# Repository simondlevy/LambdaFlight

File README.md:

# LambdaFlight
LambdaFlight is a Haskell-based flight-control package for miniature aerial
vehicles (MAVs), a.k.a.drones.  It currently works with the 
[Crazyflie](https://www.bitcraze.io/products/crazyflie-2-1/)
quadcopter and
has support for Software-In-The-Loop (SITL) simulation using
[Webots](https://cyberbotics.com/).  

To try out LambdaFlight, you'll first need to install
[Haskell](https://www.haskell.org/)
and
[NASA Copilot](https://copilot-language.github.io) (the &ldquo;secret sauce&rdquo; that
allows you to compile Haskell code to a form suitable for running on a flight 
controller.)  I was able to do this via:

```
cabal install copilot
cabal install copilot-c99
```

Then you can run a simulated
quadcopter in Webots or an actual Crazyflie, following the instructions below:

## Webots

1. Install [Webots](https://cyberbotics.com/) on your computer.  

2. Launch Webots and use <b>File / Open World</b> to open <b>Minifile/webots/worlds/simple.wbt</b>.

3. In the upper-right of the Webots app you will see a label <b>Text Editor</b> with a little file-folder
icon below it.  Use that icon to open <b>Controllers/simple/simple.cpp</b>.

4.  Build and run the code.  If you have a game controller or R/C transmitter with
adapter dongle, you can use that to fly;  otherwise, the simulator will advise you
that no such device was found and will tell you how to fly using the keyboard.

## Crazyflie

LambdaFlight takes a minimalist approach, not
supporting Crayzyflie's awesome Loco positioning or swarms, and requiriing you
to have a Crazyflie Flowdeck v2, so for running your Crazyflie you'll probably
want to use the official Crazyflie firmware. If you want to try LambdaFlight
on your Crazyflie, here's how:

1. Attach the
[Crazyflie Flowdeck v2](https://www.bitcraze.io/products/flow-deck-v2/)
to your Crazyflie board.

2. Install [STM32Duino](https://github.com/stm32duino)

3. Install the following Arduino libraries:

* [VL53L1](https://github.com/simondlevy/VL53L1)
* [PWM3901](https://github.com/simondlevy/PMW3901), <b>cross-platform</b> branch
* [BoschSensors](https://github.com/simondlevy/BoschSensors)
* [TinyEKF](https://github.com/simondlevy/TinyEKF)

4. Edit <tt>LambdaFlight/crazyflie/Makefile</tt> to reflect where you 
installed STM32Duino

5. ```cd LambdaFlight/crazyflie```

6. ```make cf2_defconfig && make links && make copilot && make -j 32```

7. ```make cload```

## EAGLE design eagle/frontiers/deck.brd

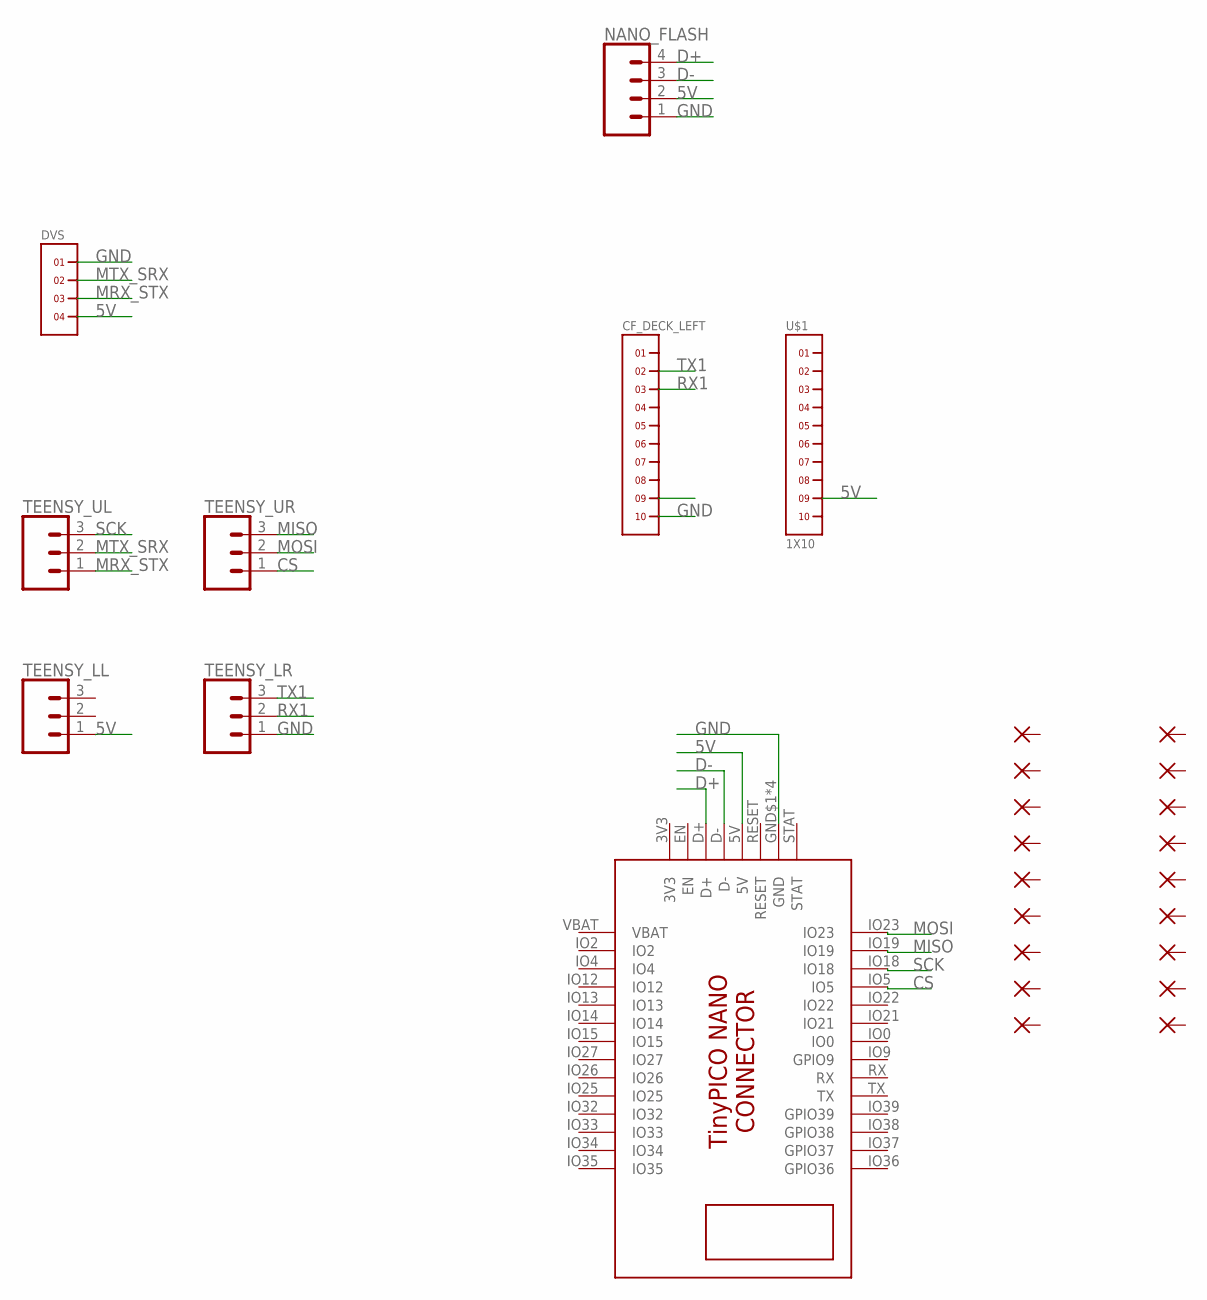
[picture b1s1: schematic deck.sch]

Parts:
CF_DECK_LEFT: 1X10
DVS: 1X4
NANO_FLASH: CONN_041X04_NO_SILK; 1X04_NO_SILK
PAD1, PAD2, PAD3, PAD4, PAD5, PAD6, PAD7, PAD8, PAD9, PAD10, PAD11, PAD12, PAD13, PAD14, PAD15, PAD16, PAD17, PAD18: SMD2; SMD1,27-2,54
TEENSY_LL: CONN_031X03_NO_SILK; 1X03_NO_SILK
TEENSY_LR: CONN_031X03_NO_SILK; 1X03_NO_SILK
TEENSY_UL: CONN_031X03_NO_SILK; 1X03_NO_SILK
TEENSY_UR: CONN_031X03_NO_SILK; 1X03_NO_SILK
U$1: 1X10
U$4: TINYPICO-NANO-CONNECTOR

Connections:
3V3: U$4.3V3
5V: DVS.4, NANO_FLASH.2, TEENSY_LL.1, U$1.9, U$4.5V
CS: TEENSY_UR.1, U$4.IO5
D+: NANO_FLASH.4, U$4.D+
D-: NANO_FLASH.3, U$4.D-
GND: CF_DECK_LEFT.10, DVS.1, NANO_FLASH.1, TEENSY_LR.1, U$4.GND$1 (GND), U$4.GND$2 (GND), U$4.GND$3 (GND), U$4.GND$4 (GND)
IO_4: CF_DECK_LEFT.9
MISO: TEENSY_UR.3, U$4.IO19
MOSI: TEENSY_UR.2, U$4.IO23
MRX_STX: DVS.3, TEENSY_UL.1
MTX_SRX: DVS.2, TEENSY_UL.2
RX1: CF_DECK_LEFT.3, TEENSY_LR.2
SCK: TEENSY_UL.3, U$4.IO18
TX1: CF_DECK_LEFT.2, TEENSY_LR.3
VBAT: U$4.VBAT

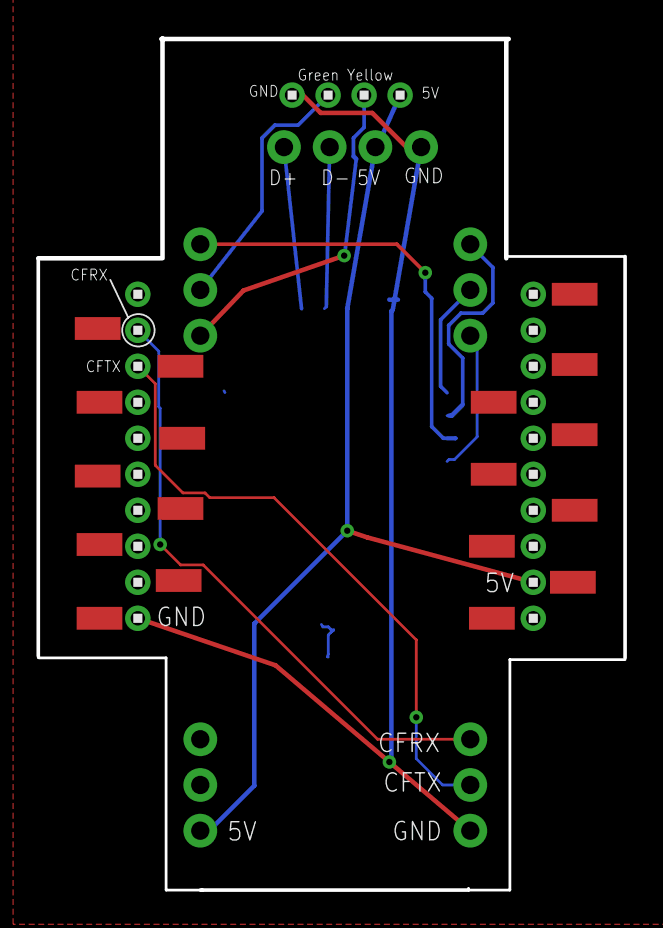
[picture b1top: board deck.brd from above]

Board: 2 copper layers, 32.6 x 47.3 mm, 27 parts (1 on the bottom side), 12 nets.

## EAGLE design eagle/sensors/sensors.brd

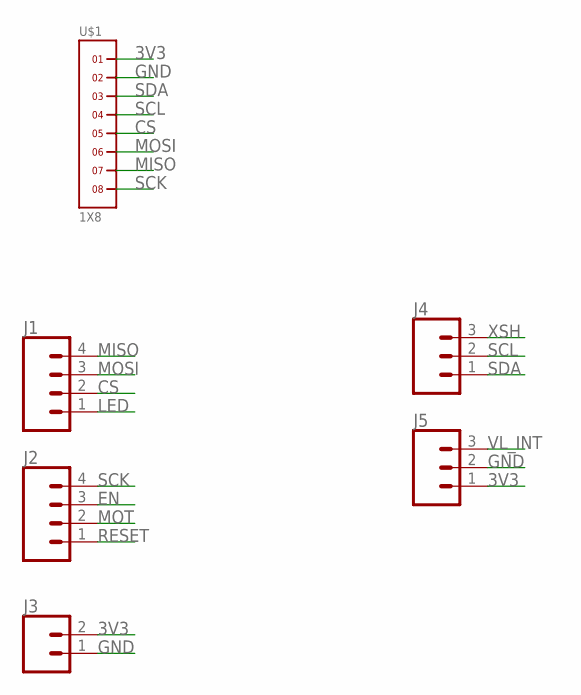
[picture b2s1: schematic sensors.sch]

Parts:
J1, J2: CONN_041X04_NO_SILK; 1X04_NO_SILK
J3: CONN_021X02_NO_SILK; 1X02_NO_SILK
J4, J5: CONN_031X03_NO_SILK; 1X03_NO_SILK
U$1: 1X8

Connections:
3V3: J3.2, J5.1, U$1.1
CS: J1.2, U$1.5
EN: J2.3
GND: J3.1, J5.2, U$1.2
LED: J1.1
MISO: J1.4, U$1.7
MOSI: J1.3, U$1.6
MOT: J2.2
RESET: J2.1
SCK: J2.4, U$1.8
SCL: J4.2, U$1.4
SDA: J4.1, U$1.3
VL_INT: J5.3
XSH: J4.3

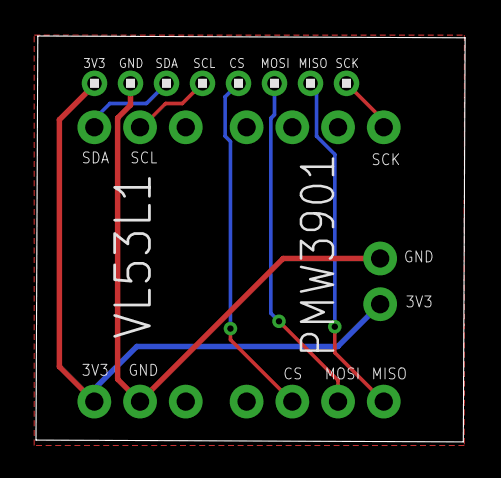
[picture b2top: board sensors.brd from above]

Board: 2 copper layers, 23.8 x 22.6 mm, 6 parts (0 on the bottom side), 8 nets.

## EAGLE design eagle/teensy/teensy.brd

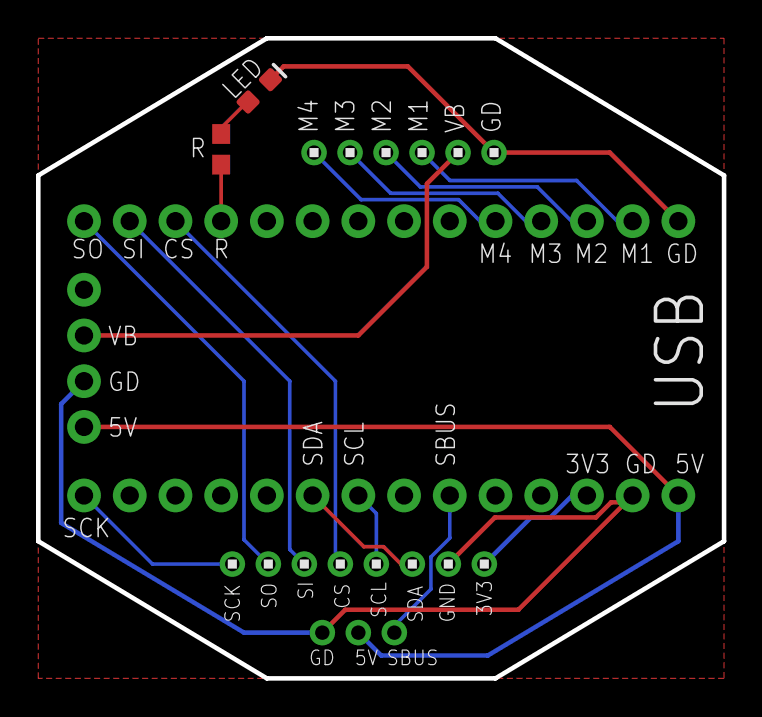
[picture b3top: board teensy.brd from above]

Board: 2 copper layers, 38.1 x 35.6 mm, 8 parts (1 on the bottom side), 17 nets.

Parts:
D1: WHITE; LED-0603
J1: 1X04_NO_SILK
J2, J3: 1X14_NO_SILK
R1: 22; 0603
U$2: 1X3
U$3: 1X8
U$4: 1X6

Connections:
3V3: J3.12, U$3.1
5V: J1.4, J3.14, U$2.2
CS: J2.3, U$3.5
GND: D1.C, J1.3, J2.14, J3.13, U$2.1, U$3.2, U$4.1
M1: J2.13, U$4.3
M2: J2.12, U$4.4
M3: J2.11, U$4.5
M4: J2.10, U$4.6
MISO: J2.1, U$3.7
MOSI: J2.2, U$3.6
R1: J2.4, R1.1
R2: D1.A, R1.2
SBUS: J3.9, U$2.3
SCK: J3.1, U$3.8
SCL: J3.7, U$3.4
SDA: J3.6, U$3.3
VBAT: J1.2, U$4.2

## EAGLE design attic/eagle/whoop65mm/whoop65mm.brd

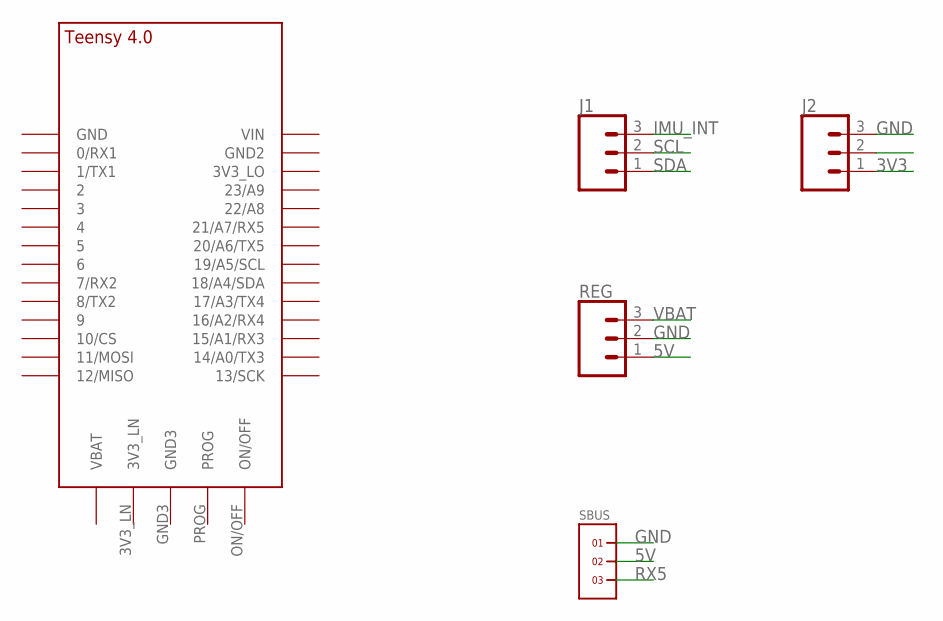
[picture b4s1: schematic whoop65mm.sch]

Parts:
J1, J2: CONN_031X03_NO_SILK; 1X03_NO_SILK
REG: CONN_031X03_NO_SILK; 1X03_NO_SILK
SBUS: 1X3
U$1: TEENSY_4.0

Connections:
3V3: J2.1
5V: REG.1, SBUS.2
GND: J2.3, REG.2, SBUS.1
IMU_INT: J1.3
RX5: SBUS.3
SCL: J1.2
SDA: J1.1
VBAT: REG.3

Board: 2 copper layers, 5 parts (0 on the bottom side), 2 nets, no tracks yet.

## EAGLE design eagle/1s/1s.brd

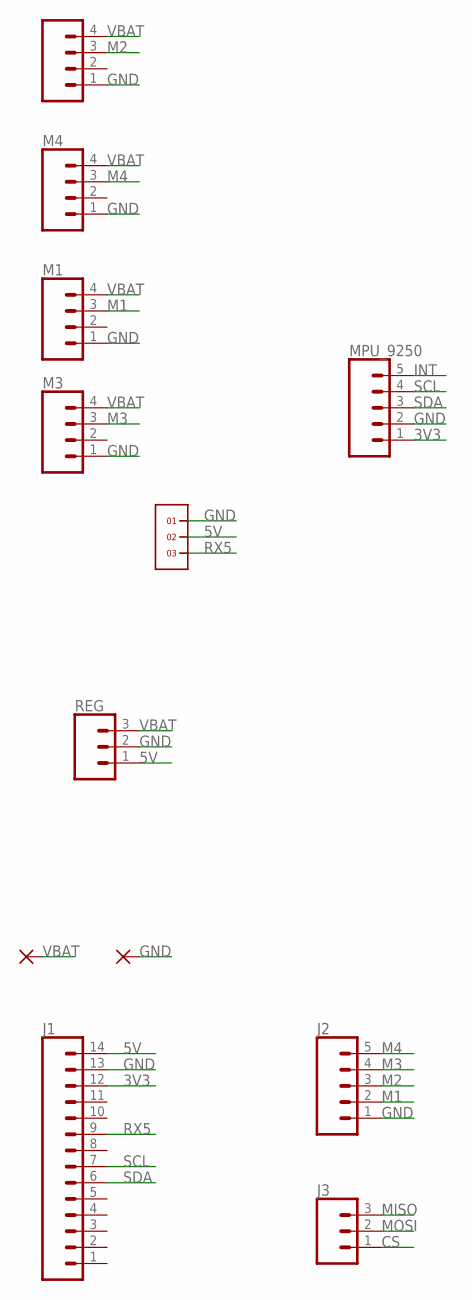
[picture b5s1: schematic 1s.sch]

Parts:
GND: SMD5; SMD2,54-5,08
J1: CONN_14NO_SILK; 1X14_NO_SILK
J2: CONN_05NO_SILK; 1X05_NO_SILK
J3: CONN_031X03_NO_SILK; 1X03_NO_SILK
M1, M2, M3, M4: CONN_041X04_NO_SILK; 1X04_NO_SILK
MPU_9250: CONN_05NO_SILK; 1X05_NO_SILK
REG: CONN_031X03_NO_SILK; 1X03_NO_SILK
SBUS_RX: 1X3
VBAT: SMD5; SMD2,54-5,08

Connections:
3V3: J1.12, MPU_9250.1
5V: J1.14, REG.1, SBUS_RX.2
CS: J3.1
GND: GND.1, J1.13, J2.1, M1.1, M2.1, M3.1, M4.1, MPU_9250.2, REG.2, SBUS_RX.1
INT: MPU_9250.5
M1: J2.2, M1.3
M2: J2.3, M2.3
M3: J2.4, M3.3
M4: J2.5, M4.3
MISO: J3.3
MOSI: J3.2
RX5: J1.9, SBUS_RX.3
SCL: J1.7, MPU_9250.4
SDA: J1.6, MPU_9250.3
VBAT: M1.4, M2.4, M3.4, M4.4, REG.3, VBAT.1

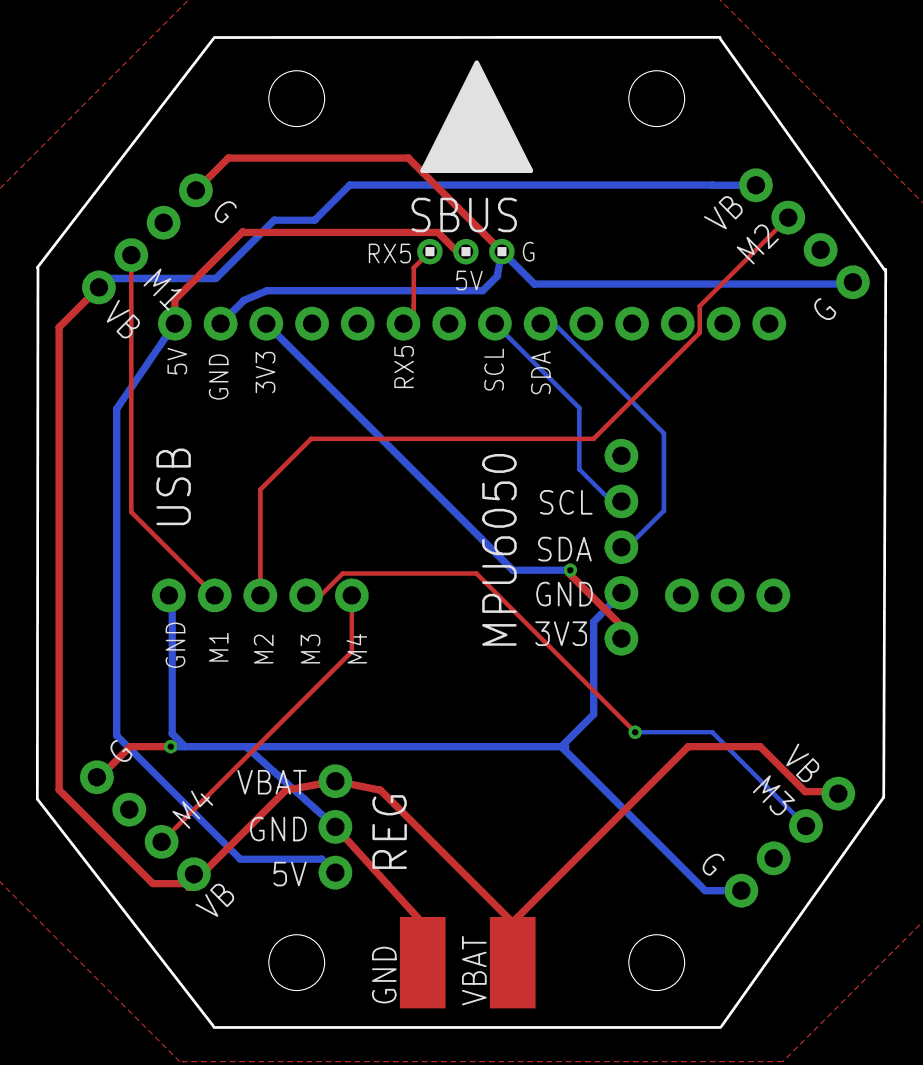
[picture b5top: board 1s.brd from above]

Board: 2 copper layers, 47.1 x 55.0 mm, 12 parts (0 on the bottom side), 11 nets.

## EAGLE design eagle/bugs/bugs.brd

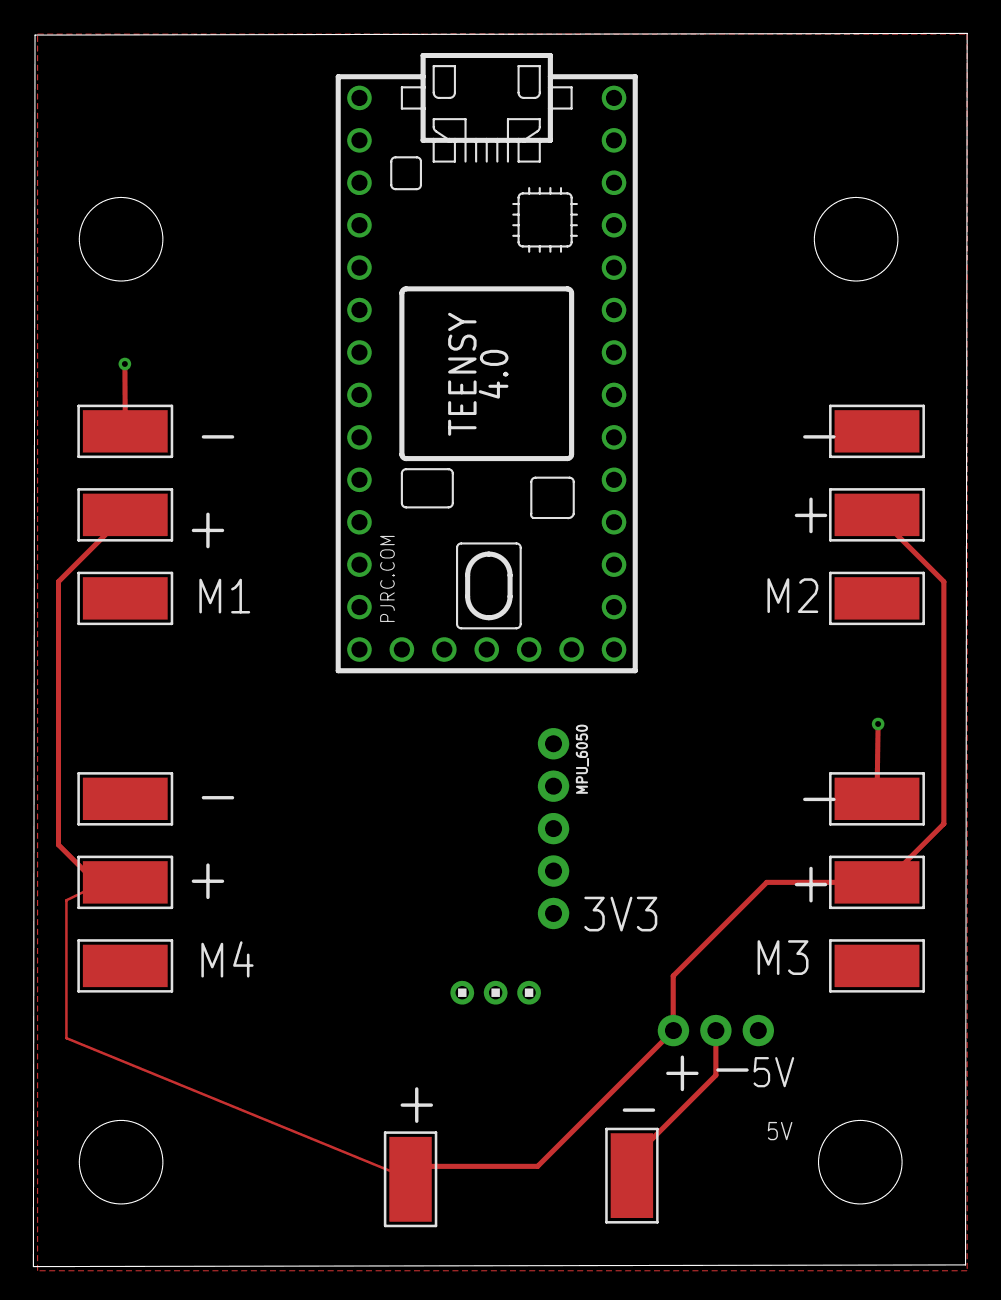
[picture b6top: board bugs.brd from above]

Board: 2 copper layers, 55.9 x 73.8 mm, 18 parts (0 on the bottom side), 10 nets.

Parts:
GND, GND1, GND2, GND3, GND4: WIREPADSMD5-2,5; 5-2,5
M1, M2, M3, M4: WIREPADSMD5-2,5; 5-2,5
MPU_6050: 1X05_NO_SILK
REG: REG; 1X03_NO_SILK
SBUS_RX: 1X3
U$1: TEENSY_4.0
VBAT, VBAT1, VBAT2, VBAT3, VBAT4: WIREPADSMD5-2,5; 5-2,5

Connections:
5V: REG.1, SBUS_RX.2, U$1.VIN
GND: GND.1, GND1.1, GND2.1, GND3.1, GND4.1, MPU_6050.4, REG.2, SBUS_RX.1, U$1.GND, U$1.GND2
M1: M1.1, U$1.0/RX
M2: M2.1, U$1.1/TX
M3: M3.1, U$1.2
M4: M4.1, U$1.3/CANTX
RX5: SBUS_RX.3, U$1.21/A7
SCL: MPU_6050.2, U$1.19/A5/SCL
SDA: MPU_6050.3, U$1.18/A4/SDA
VBAT: REG.3, VBAT.1, VBAT1.1, VBAT2.1, VBAT3.1, VBAT4.1

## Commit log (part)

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2024-04-19 =More Ekf.hs
2024-04-19 =More teensy_ekf.hpp
2024-04-20 modified: ../../haskell/Ekf.hs
2024-04-22 Removed _isUpdated, shouldFinalize flags
2024-04-23 new file: ../../haskell/MinEkf.hs
2024-04-23 =More MinEkf.hs work
2024-04-23 Fixed referential cycle in Ekf.hs
2024-04-23 =Cleanup
2024-04-24 Begin using BasicLinearAlgebra library
2024-04-24 =More BasicLinearAlgebra
2024-04-24 new file: src/ekf_noquat.hpp
2024-04-24 =More ekf_noquat.hpp
2024-04-28 Restored linalg.h
2024-04-28 Restored Core.hs for sim
2024-04-28 Sim working again
2024-04-29 Sim uses Crazyflie.hs instead of Core.hs
2024-04-29 renamed: ../src/ekf_noquat.hpp -> ../attic/src/ekf_noquat.hpp
2024-04-29 modified: README.md
2024-04-30 new file: old_usfs/old_usfs.ino
2024-04-30 =More usfs.ino
2024-04-30 imuviz exits on ESC
2024-04-30 modified: eagle/sensors/sensors.brd
2024-05-01 modified: ../../src/teensy_ekf.hpp
2024-05-01 typename => typeName
2024-05-01 Added rangefinder
2024-05-01 Cleanup
2024-05-01 Moved rangefinder measurement model into EKF
2024-05-02 new file: new_usfs/new_usfs.ino
2024-05-02 =More new_usfs.ino
2024-05-02 modified: ../imuviz.py
2024-05-02 More usfs.ino
2024-05-03 Work on Haskell EKF
2024-05-03 =More EKF work
2024-05-04 =More Haskell quaternion work
2024-05-04 new file: ../../haskell/TeensyUsfs.hs
2024-05-05 Adjusted motor pins
2024-05-05 renamed: usfs.ino -> teensy.ino
2024-05-05 Swap quaternion qw/qx, qy/qz for upside-down USFS mounting
2024-05-05 Restart rangefinder work
2024-05-05 new file: ../attic/src/teensy_ekf.hpp
2024-05-06 Crazyflie gets state Z directly from rangefinder
2024-05-06 Crazyflie sends Z, DX, DY, DZ to client
2024-05-06 More teensy_ekf
2024-05-06 =More teensy_ekf
2024-05-06 Use vl53l1-arduino library
2024-05-06 new file: madgwick/madgwick.ino
2024-05-06 Begin Z,DZ estimation in Haskell
2024-05-06 =More Teensy.hs
2024-05-06 More DZ sensor fusion
2024-05-07 renamed: teensy.ino -> main/main.ino
2024-05-07 Begin calibration sketch
2024-05-07 =More calibration work
2024-05-07 Do calibration directly in teensy.ino
2024-05-07 new file: teensy/ekf.hpp
2024-05-07 More Teensy EKF
2024-05-07 Start newekf.hpp
2024-05-07 =More newekf
2024-05-07 newekf.hpp => ekf.hpp
2024-05-07 =More Ekf class
2024-05-07 new file: src/newekf.hpp
2024-05-07 =More ekf
2024-05-08 modified: src/newekf.hpp
2024-05-08 Restart Ekf class
2024-05-08 More EKF class
2024-05-09 new file: src/crazyflie_ekf.hpp
2024-05-09 =More Ekf superclass
2024-05-09 Restored Teensy
2024-05-09 Accomodate USFS orientation in Haskell
2024-05-09 LED stays on while vehicle is armed
2024-05-09 =More CrazyflieEkf
2024-05-09 More CrazyflieEkf
2024-05-10 new file: src/crazyflie_ekf.cpp
2024-05-10 Use TinyEKF
2024-05-10 Works with new TinyEKF
2024-05-10 Removed isFlying flag from EKF/estimator
2024-05-10 Isolate nextPredictionMsec to Crazyflie
2024-05-10 Moved dt computation out of TinyEkf::predict()
2024-05-11 modified: src/ekf.cpp
2024-05-11 Moved prediction update time check out of TinyEkf
2024-05-11 Simplified matrix_t, vector_t
2024-05-11 More TinyEkf
2024-05-11 =More TinyEKF
2024-05-11 Adjust Euler angles for X90
2024-05-11 Works with updated PMW3901 library
2024-05-11 More Ekf
2024-05-11 new file: src/ekf.hpp
2024-05-11 Pass r to TinyEkf::update()
2024-05-11 Pass mesured, predicted to TinyEkf::update()
2024-05-11 Added EKF_M = 3
2024-05-12 tinyekf.hpp => ekftiny.hpp
2024-05-12 ekftiny.hpp => tinyekf.hpp
2024-05-12 deleted: ../haskell/Motors.hs
2024-05-12 Renamed QuadX motors with directions rather than numbers
2024-05-12 More mixer work
2024-05-12 Renamed motor pins with directions
2024-05-13 Uses new TinyEKF
2024-05-13 ekf.getState() => ekf.get()
2024-05-16 new file: src/tinyekf.hpp
2024-05-16 modified: src/ekf.hpp
2024-05-16 Uses ekf_cleanup_covariance()
2024-05-16 Uses ekf_scalar_update()
2024-05-16 EKF_CUSTOM
2024-05-16 Removed Teensy stuff
2024-05-16 deleted: Teensy.hs
2024-05-17 Use ekf_custom_* calls
2024-05-17 Uses updated tinyekf
2024-05-17 Use tinyekf_custom.h
2024-05-18 Fixed webots Makefile
2024-05-18 Working on broken open-loop roll/pitch demands
2024-05-19 new file: frontiers/deck.brd
2024-07-19 new file: src/hal/pmw3901.cpp
2024-09-01 new file: Makefile
2024-10-29 modified: crazyflie/src/ekf.hpp
2025-03-02 new file: src/tasks/rpi.hpp
2025-03-02 modified: src/tasks/rpi.hpp
2025-03-03 Use uart1 instead of uart2 for RPi comms
2025-03-04 new file: make.sh
2025-03-04 modified: deck/Kconfig

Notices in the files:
parts and their libraries:
SparkFun-Connectors: Licensing: Creative Commons ShareAlike 4.0 International - https://creativecommons.org/licenses/by-sa/4.0
